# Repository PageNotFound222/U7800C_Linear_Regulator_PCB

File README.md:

# U7800C Linear Regulator PCB Design
The 7800 series (78xx) is a family of three-terminal linear voltage regulators designed to provide a fixed, stable positive output voltage from a higher, unregulated input voltage
## Overview
This project is a PCB design of a linear voltage regulator based on the U7800C series.
The board provides a regulated DC output from a higher DC input and was designed
as a learning project to practice schematic capture, PCB layout, and power routing
fundamentals using KiCad.
## Specifications
- Regulator: U7800C (7805 variant)
- Input Voltage: 7 V – 20 V
- Output Voltage: 5 V
- Output Current: up to 1 A (with proper thermal dissipation)
- Package: TO-220
- PCB Layers: 2-layer
## Design Details
- Schematic implemented using the datasheet typical application circuit
- Input and output decoupling capacitors placed close to regulator pins
- Through-hole components selected for ease of assembly and learning
- Input and output screw terminal connectors for external wiring
## Files Included
- KiCad schematic and PCB files
- Gerber and drill files (fabrication-ready)
- Schematic and PCB layout screenshots
- Manufacturer datasheet
## Learning Objectives
- Reading and applying datasheet application circuits
- Selecting correct packages and footprints
- Understanding grounding and decoupling in linear regulators
- Converting schematic designs into manufacturable PCBs
## Status
✔ Completed  
✔ ERC/DRC clean  
✔ Ready for fabrication  
## Tools Used
- KiCad

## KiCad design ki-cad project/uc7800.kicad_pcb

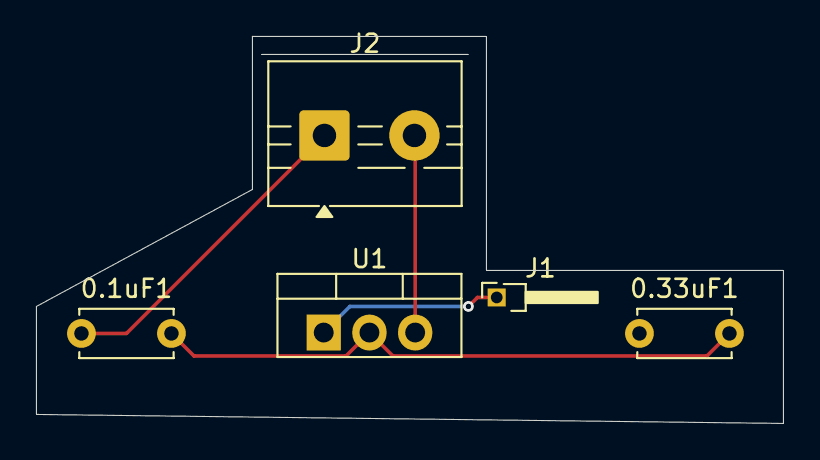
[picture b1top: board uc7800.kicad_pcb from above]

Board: 2 copper layers, 41.5 x 21.5 mm, 5 parts (0 on the bottom side), 4 nets.

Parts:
0.1uF1: C_US; C_Disc_D5.0mm_W2.5mm_P5.00mm
0.33uF1: C_Small_US; C_Disc_D5.0mm_W2.5mm_P5.00mm
J1: Conn_01x02; PinHeader_1x01_P1.27mm_Horizontal
J2: Conn_01x02; TerminalBlock_MaiXu_MX126-5.0-02P_1x02_P5.00mm
U1: LM7805_TO220; TO-220-3_Vertical

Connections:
+V: J1.1, U1.1 (VI)
+Vo: J2.2, U1.3 (VO)
GND: 0.1uF1.2, 0.33uF1.2, U1.2 (GND)
unnamed: 0.1uF1.1, J2.1
